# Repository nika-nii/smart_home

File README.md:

# smart_home
 Умный дом от глупых разработчиков

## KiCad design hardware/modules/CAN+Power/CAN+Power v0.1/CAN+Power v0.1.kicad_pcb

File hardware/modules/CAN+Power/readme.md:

# Модуль питания узла + физический уровень CAN
## Схема (скоро...) 
## Список компонентов

|№  | Компонент | Обозначение на схеме | Ссылка | Кол-во | Цена |
|:--|:---------:|:--------------------:|:------:|:------:|:----:|
|  1|CAN PHY SN65HVD230|                      |http://www.ti.com/lit/ds/symlink/sn65hvd230.pdf https://www.aliexpress.ru/item/32876127359.html|1|25 руб/шт|
|  2,3,6,7,9| Резистор SMD 1206 10K,120,18K,11K,0.3 Ом|                      |https://aliexpress.ru/item/32949400804.html https://aliexpress.ru/item/32840478325.html|около 10|около 1 руб/шт|
|  4| Клеммы 4 пина|                      |https://aliexpress.ru/item/32942971002.html|1| 8 руб/шт|
|  5|DC\DC Преобразователь MC33063|                      |http://www.ti.com/lit/ds/symlink/mc34063a.pdf https://www.aliexpress.ru/item/33047422937.html|1| 7 руб/шт|
|  8|Диод 1N5819|                      |https://aliexpress.ru/item/32849879904.html|1| 0.6 руб/шт|
|  9|Конденсатор 1206 270pf|                      |https://aliexpress.ru/item/4000096072838.html|1| 0.6 руб/шт|
|  10|Катушка индуктивности SMD 47uH **???** |                      |https://aliexpress.ru/item/32879744663.html|1| 12 руб/шт|
|  11|Конденсатор электролитический 16v 100uF|                      |https://aliexpress.ru/item/33013972369.html|1| 4 руб/шт|
|  12|Конденсатор электролитический 16v 220uF|                      |https://aliexpress.ru/item/33013972369.html|1| 4 руб/шт|
| 13 |Конденсатор керамический 50v 100nF|                      |https://aliexpress.ru/item/4000096111520.html|1| 0.7 руб/шт|
| 14 |Фильтр ЭМИ| *опционально* |https://aliexpress.ru/item/32855698256.html|1| 6 руб |

...

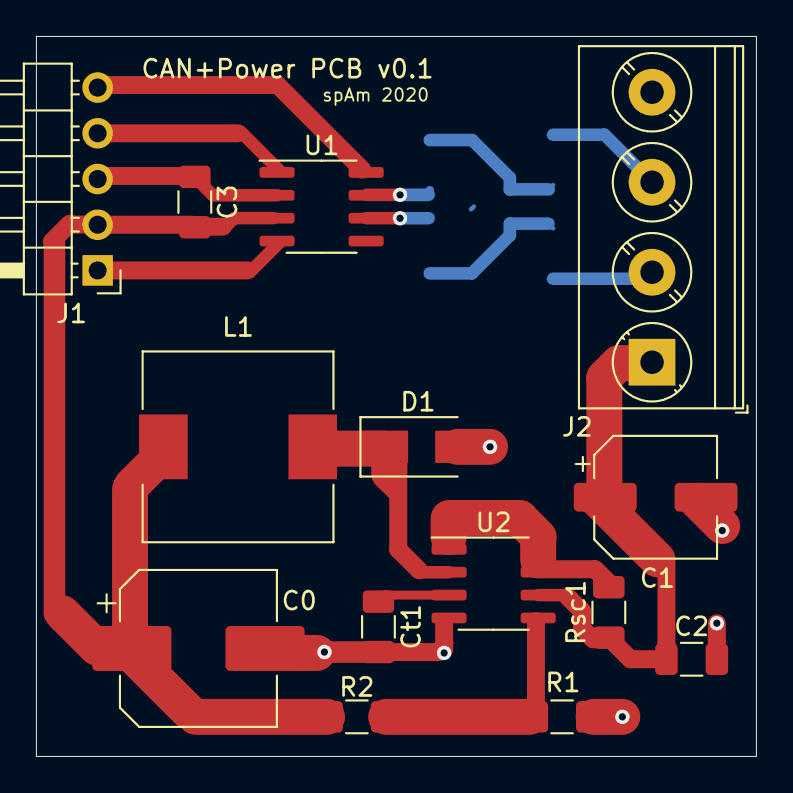
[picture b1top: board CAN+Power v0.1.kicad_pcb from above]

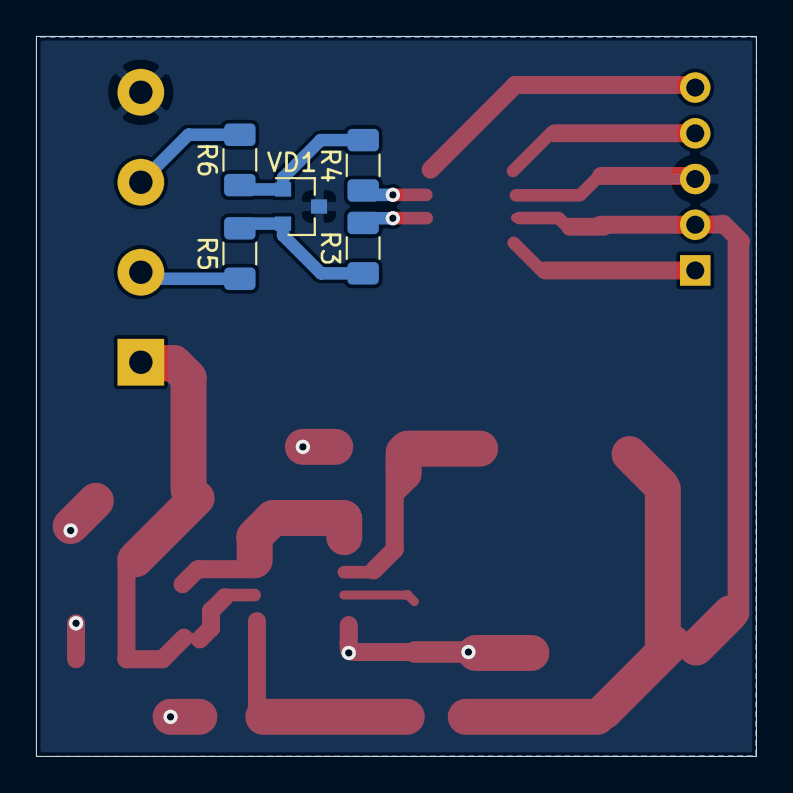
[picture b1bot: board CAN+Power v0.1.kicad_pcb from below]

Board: 2 copper layers, 40.0 x 40.0 mm, 19 parts (5 on the bottom side), 12 nets.

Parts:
C1: 100uF; CP_Elec_6.3x5.4
C2, C3: 100nF; C_1206_3216Metric
Ct1: 270pF; C_1206_3216Metric
D1: 1N5819; D_SMA
J1: Conn_01x05_Male; PinHeader_1x05_P2.54mm_Horizontal
J2: 1; TerminalBlock_Phoenix_PT-1,5-4-5.0-H_1x04_P5.00mm_Horizontal
L1: 47uH; L_10.4x10.4_H4.8
R1: 11k; R_1206_3216Metric
R2: 18k; R_1206_3216Metric
R3, R4, R5, R6: R_1206_3216Metric
Rsc1: 0.3 Ohm; R_1206_3216Metric
U1: SN65HVD230; SOIC-8_3.9x4.9mm_P1.27mm
U2: MC33063AD; SOIC-8_3.9x4.9mm_P1.27mm
VD1: SOT-23
С0: 220uF; CP_Elec_8x10.5

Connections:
3.3+: C3.2, J1.2, L1.2, R2.2, U1.3, С0.1
CAN+: J2.3, R6.2
CAN-: J2.2, R5.1
CAN_RXD: J1.1, U1.4
CAN_TXD: J1.4, U1.1
GND: C1.2, C2.2, C3.1, Ct1.2, D1.2, J1.3, J2.4, R1.2, U1.2, U2.4, VD1.3, С0.2
MODE: J1.5, U1.8
unnamed: C1.1, C2.1, J2.1, Rsc1.1, U2.6
unnamed: Ct1.1, U2.3
unnamed: D1.1, L1.1, U2.2
unnamed: R1.1, R2.1, U2.5
unnamed: Rsc1.2, U2.1, U2.7, U2.8

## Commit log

2019-10-13 Мысли на текущий момент
2019-10-13 Новые штуки про сети
2020-03-10 список компонентов для CAN+Power
2020-03-10 исправление в readme
2020-03-10 синхронизация между пк
2020-03-11 Импровизированнй "BOM" готов
2020-03-11 добавил керамику на входе, начал схему
2020-03-11 готова схема dc\dc
2020-03-11 готова
2020-03-16 готово
2020-03-21 плата готова и заказана
2020-06-22 шаблон есть
2020-06-22 начал шлюз
